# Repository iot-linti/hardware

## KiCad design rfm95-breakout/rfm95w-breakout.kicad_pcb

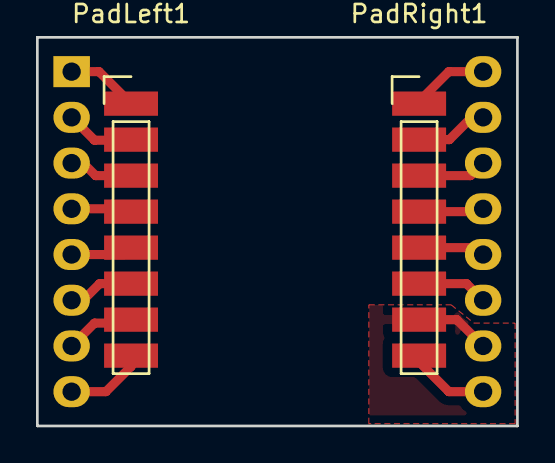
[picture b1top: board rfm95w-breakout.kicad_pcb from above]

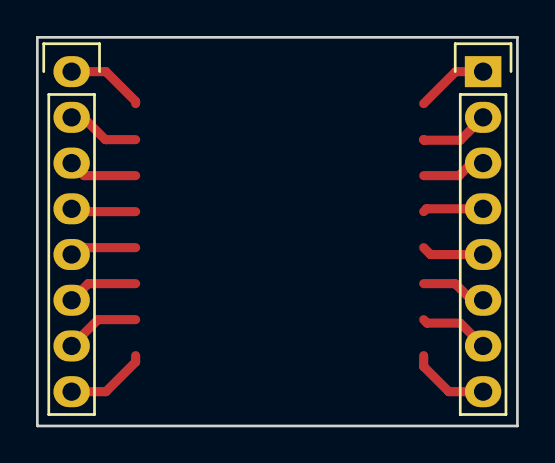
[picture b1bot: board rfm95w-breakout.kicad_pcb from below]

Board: 2 copper layers, 26.7 x 21.6 mm, 4 parts (2 on the bottom side), 16 nets.

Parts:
PadLeft1: CONN_01X08; Pin_Header_Straight_1x08_Pitch2.00mm
PadRight1: CONN_01X08; Pin_Header_Straight_1x08_Pitch2.00mm
PinLeft1: CONN_01X08; Pin_Header_Straight_1x08
PinRight1: CONN_01X08; Pin_Header_Straight_1x08

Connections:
unnamed: PadLeft1.1, PinLeft1.1
unnamed: PadLeft1.2, PinLeft1.2
unnamed: PadLeft1.3, PinLeft1.3
unnamed: PadLeft1.4, PinLeft1.4
unnamed: PadLeft1.5, PinLeft1.5
unnamed: PadLeft1.6, PinLeft1.6
unnamed: PadLeft1.7, PinLeft1.7
unnamed: PadLeft1.8, PinLeft1.8
unnamed: PadRight1.1, PinRight1.1
unnamed: PadRight1.2, PinRight1.2
unnamed: PadRight1.3, PinRight1.3
unnamed: PadRight1.4, PinRight1.4
unnamed: PadRight1.5, PinRight1.5
unnamed: PadRight1.6, PinRight1.6
unnamed: PadRight1.7, PinRight1.7
unnamed: PadRight1.8, PinRight1.8

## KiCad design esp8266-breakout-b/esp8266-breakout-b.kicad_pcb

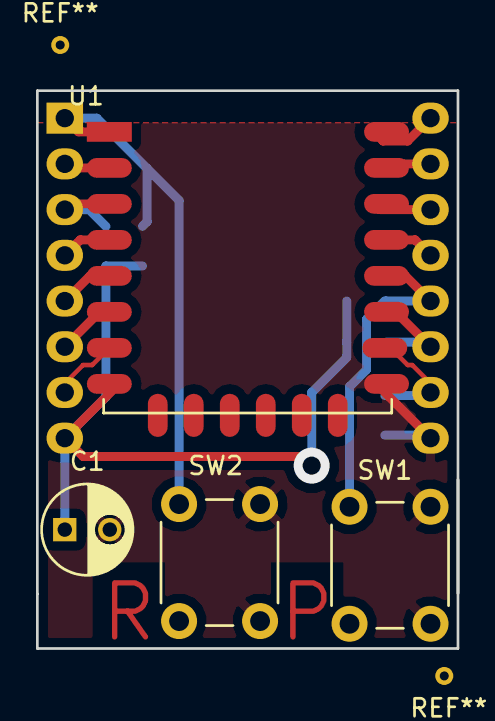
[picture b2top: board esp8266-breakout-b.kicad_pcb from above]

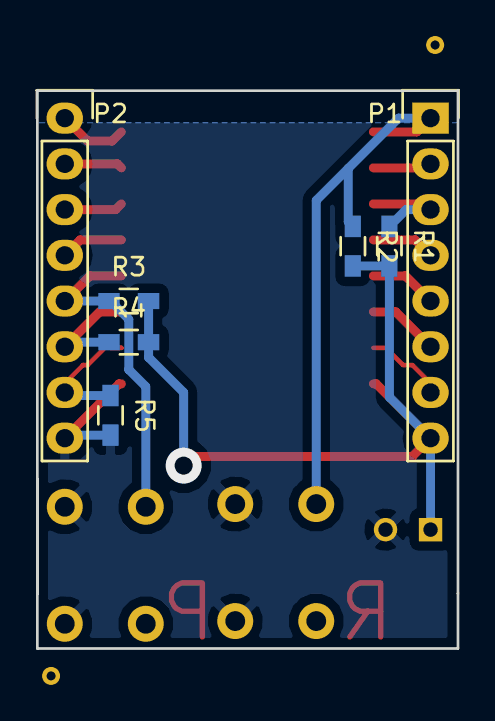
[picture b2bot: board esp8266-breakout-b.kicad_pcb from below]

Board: 2 copper layers, 23.4 x 31.0 mm, 11 parts (7 on the bottom side), 16 nets.

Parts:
C1: 10uF; C_Radial_D5_L6_P2.5
P1, P2: CONN_01X08; Pin_Header_Straight_1x08
R1, R2, R3, R4, R5: 47k; R_0603_HandSoldering
SW1, SW2: SW_Push; SW_PUSH_6mm
U1: ESP-12E

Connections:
+3V3: C1.1, P1.8, R1.2, R2.2, R3.2, R4.2, U1.8
GND: C1.2, P2.8, R5.2, SW1.1, SW2.2, U1.9
unnamed: P1.1, R2.1, SW2.1, U1.1
unnamed: P1.2, U1.2
unnamed: P1.3, R1.1, U1.3
unnamed: P1.4, U1.4
unnamed: P1.5, U1.5
unnamed: P1.6, U1.6
unnamed: P1.7, U1.7
unnamed: P2.1, U1.16
unnamed: P2.2, U1.15
unnamed: P2.3, U1.14
unnamed: P2.4, U1.13
unnamed: P2.5, R3.1, SW1.2, U1.12
unnamed: P2.6, R4.1, U1.11
unnamed: P2.7, R5.1, U1.10

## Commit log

2017-10-21 Easy to setup breakout for esp8266 esp12 modules
2017-11-07 rfm95w breakout for protoboard
2018-01-11 rak831 initial version
2018-01-16 Versión invertida y con pistas más gruesas.
2018-01-29 Versión más compacta
